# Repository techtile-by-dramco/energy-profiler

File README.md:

# 🔍 Energy Profiler 🔍

This repository contains 
- the **hardware** files (including the controller board)
- the **firmware** running on the controller board
- the **publisher script** (which receives information from the controller board over a USB connection)
- an example **subscriber script**

### Updates ToDo 📝
- ???

### Test Energy Profiler script
1. Test `/publisher-script/main_last.py`
2. Run services
	1. Copy service files to systemd:
	```
	sudo cp ~/energy-profiler/ep.service /lib/systemd/system/
 	```
 	2. Enable and start services
  	```
   	sudo systemctl enable ep.service
   	sudo systemctl start ep.service
  	```   
### Update energy profiler service
	
```
sudo cp ~/energy-profiler/ep.service /etc/systemd/system/
sudo systemctl daemon-reload
sudo systemctl restart ep.service
```

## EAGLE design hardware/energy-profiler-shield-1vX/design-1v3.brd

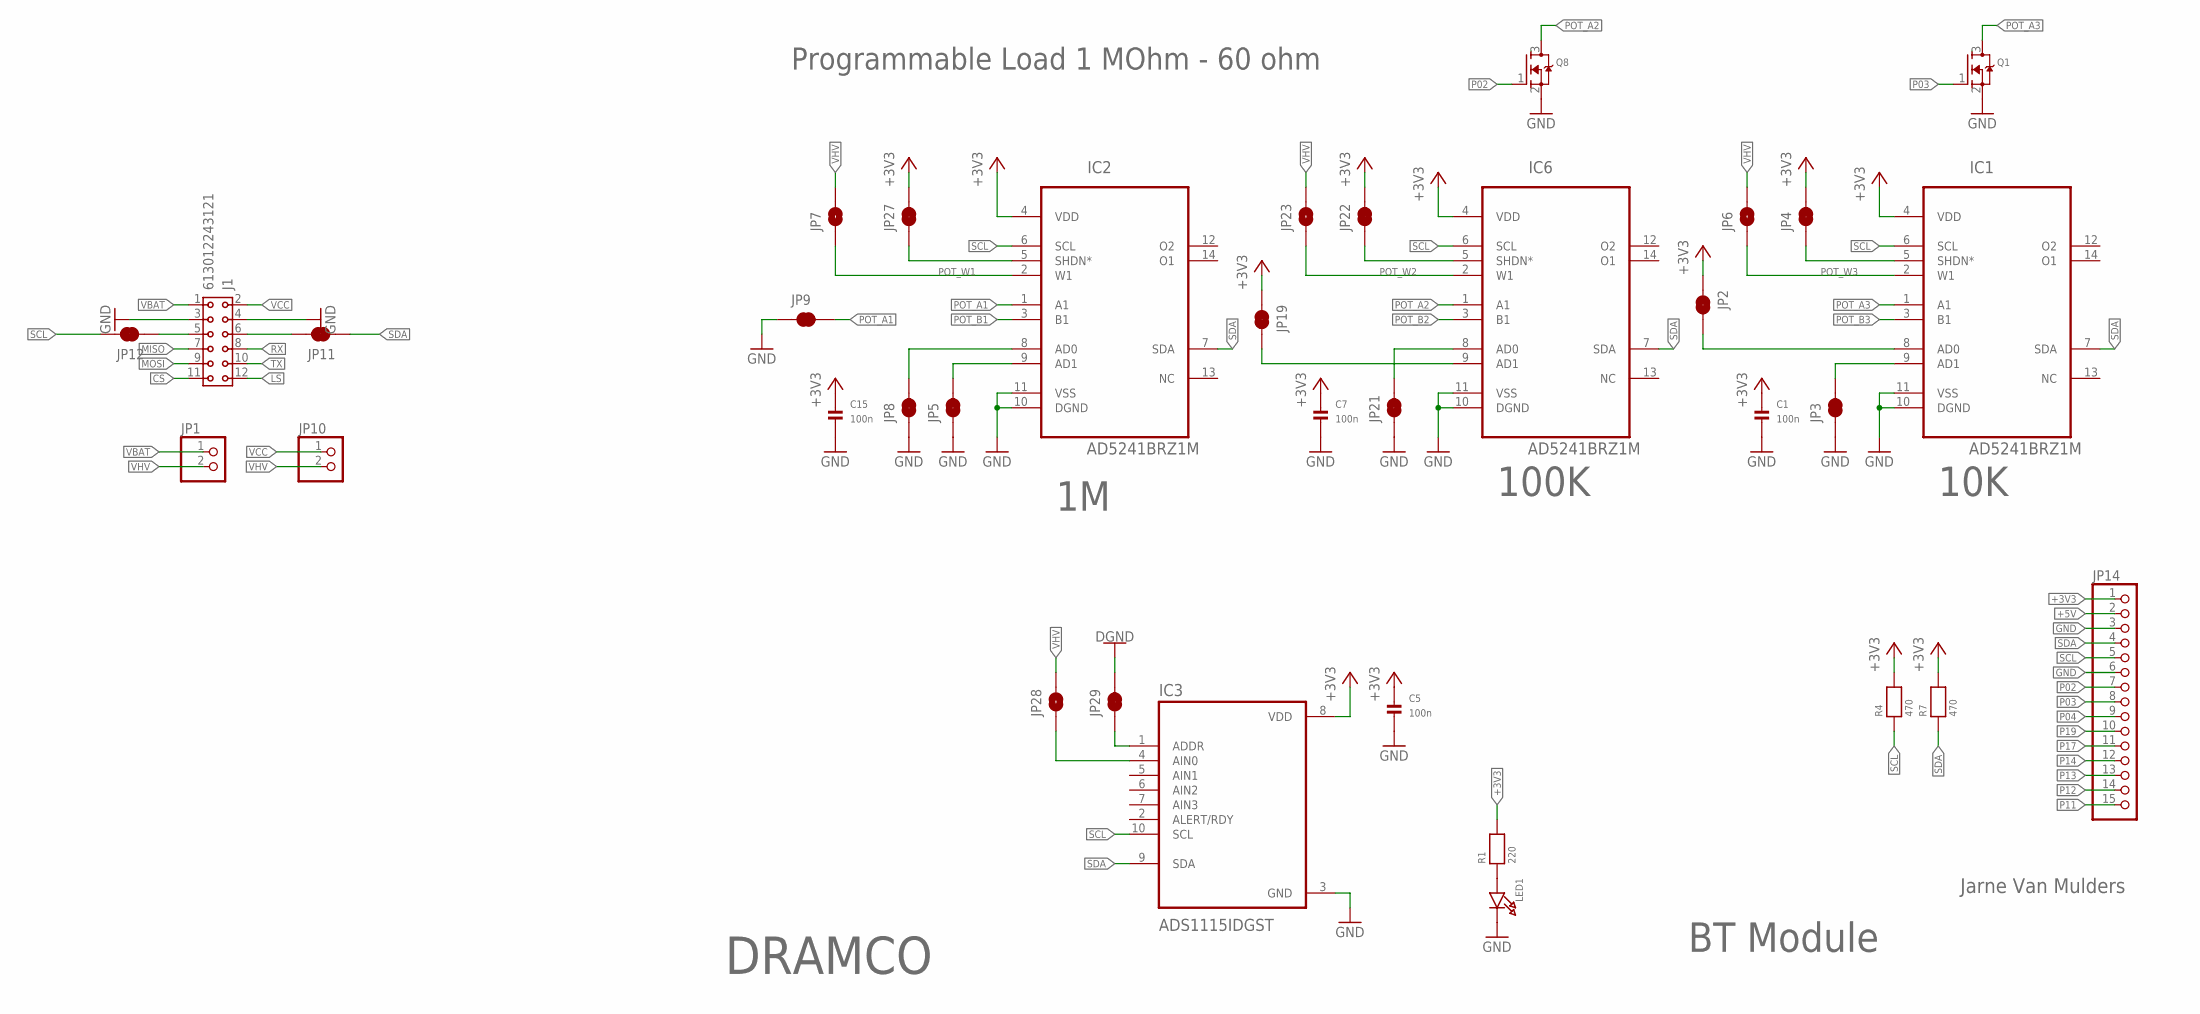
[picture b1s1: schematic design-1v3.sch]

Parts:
C1, C5, C7, C15: 100n; 0603
IC1, IC2, IC6: AD5241BRZ1M; SOIC127P600X175-14N
IC3: ADS1115IDGST; SOP50P490X110-10N
J1: 613012243121
JP1, JP10: HEADER-1X2ROUND; 1X02_ROUND
JP2, JP3, JP4, JP5, JP8, JP9, JP11, JP12, JP19, JP21, JP22, JP27, JP29: JUMPER-SMT_2_NC_TRACE_NO-SILK; SMT-JUMPER_2_NC_TRACE_NO-SILK
JP6, JP7, JP23, JP28: JUMPER-SMT_2_NO_NO-SILK; SMT-JUMPER_2_NO_NO-SILK
JP14: HEADER-1X15; 1X15_ROUND_70
LED1: LED0805; CHIPLED_0805
Q1, Q8: MOSFET-NREFLOW; SOT23-R
R1: 220; 0603
R4, R7: 470; 0603

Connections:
+3V3: C1.1, C5.1, C7.1, C15.1, IC1.4 (VDD), IC2.4 (VDD), IC3.8 (VDD), IC6.4 (VDD), JP2.1, JP4.2, JP14.1, JP19.1, JP22.2, JP27.2, R1.2, R4.2, R7.2
+5V: JP14.2
CS: J1.11
GND: C1.2, C5.2, C7.2, C15.2, IC1.10 (DGND), IC1.11 (VSS), IC2.10 (DGND), IC2.11 (VSS), IC3.3 (GND), IC6.10 (DGND), IC6.11 (VSS), J1.3, J1.4, JP3.1, JP5.1, JP8.1, JP9.1, JP14.3, JP14.6, JP21.1, JP29.2, LED1.C, Q1.2 (S), Q8.2 (S)
LS: J1.12
MISO: J1.7
MOSI: J1.9
unnamed: IC1.8 (AD0), JP2.2
unnamed: IC1.9 (AD1), JP3.2
unnamed: IC1.5 (SHDN*), JP4.1
unnamed: J1.5, JP12.1
unnamed: J1.6, JP11.2
unnamed: IC6.9 (AD1), JP19.2
unnamed: IC6.8 (AD0), JP21.2
unnamed: IC2.5 (SHDN*), JP27.1
unnamed: IC2.8 (AD0), JP8.2
unnamed: IC2.9 (AD1), JP5.2
unnamed: LED1.A, R1.1
unnamed: IC3.4 (AIN0), JP28.1
unnamed: IC3.1 (ADDR), JP29.1
unnamed: IC6.5 (SHDN*), JP22.1
P02: JP14.7, Q8.1 (G)
P03: JP14.8, Q1.1 (G)
P04: JP14.9
P11: JP14.15
P12: JP14.14
P13: JP14.13
P14: JP14.12
P17: JP14.11
P19: JP14.10
POT_A1: IC2.1 (A1), JP9.2
POT_A2: IC6.1 (A1), Q8.3 (D)
POT_A3: IC1.1 (A1), Q1.3 (D)
POT_B1: IC2.3 (B1)
POT_B2: IC6.3 (B1)
POT_B3: IC1.3 (B1)
POT_W1: IC2.2 (W1), JP7.1
POT_W2: IC6.2 (W1), JP23.1
POT_W3: IC1.2 (W1), JP6.1
RX: J1.8
SCL: IC1.6 (SCL), IC2.6 (SCL), IC3.10 (SCL), IC6.6 (SCL), JP12.2, JP14.5, R4.1
SDA: IC1.7 (SDA), IC2.7 (SDA), IC3.9 (SDA), IC6.7 (SDA), JP11.1, JP14.4, R7.1
TX: J1.10
VBAT: J1.1, JP1.1
VCC: J1.2, JP10.1
VHV: JP1.2, JP6.2, JP7.2, JP10.2, JP23.2, JP28.2

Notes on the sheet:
BT Module
Jarne Van Mulders
DRAMCO
100K
10K
Programmable Load 1 MOhm - 60 ohm

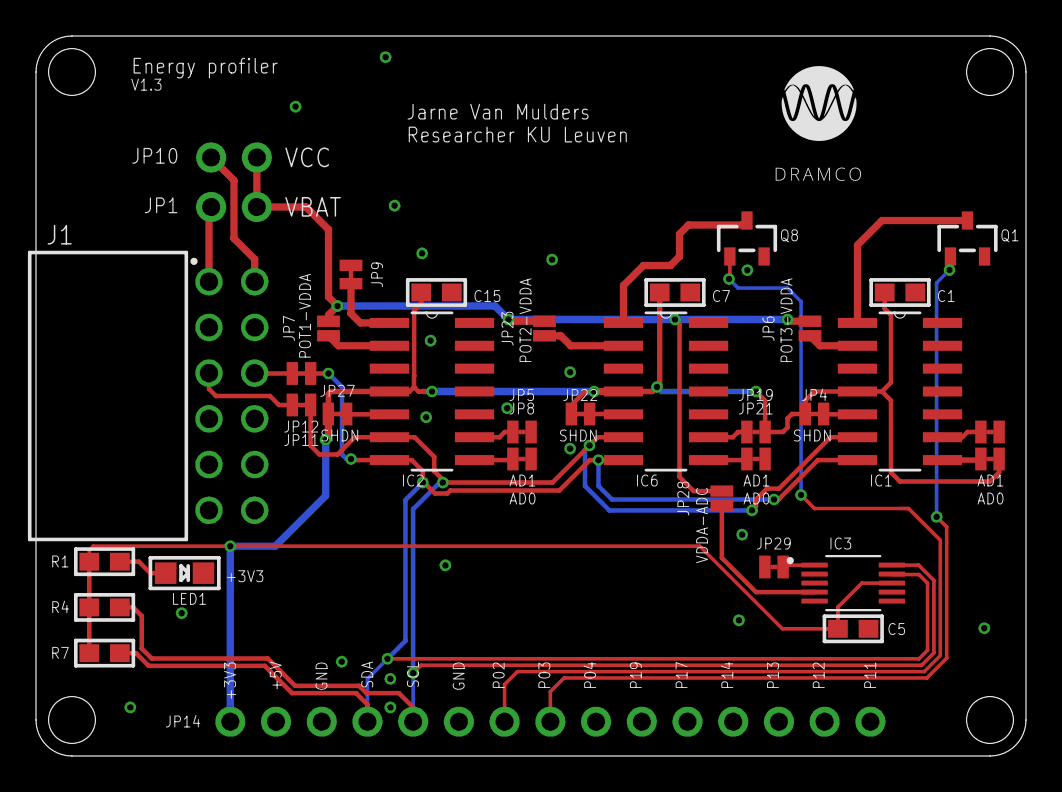
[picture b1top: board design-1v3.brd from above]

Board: 2 copper layers, 55.0 x 40.0 mm, 35 parts (0 on the bottom side), 29 nets.

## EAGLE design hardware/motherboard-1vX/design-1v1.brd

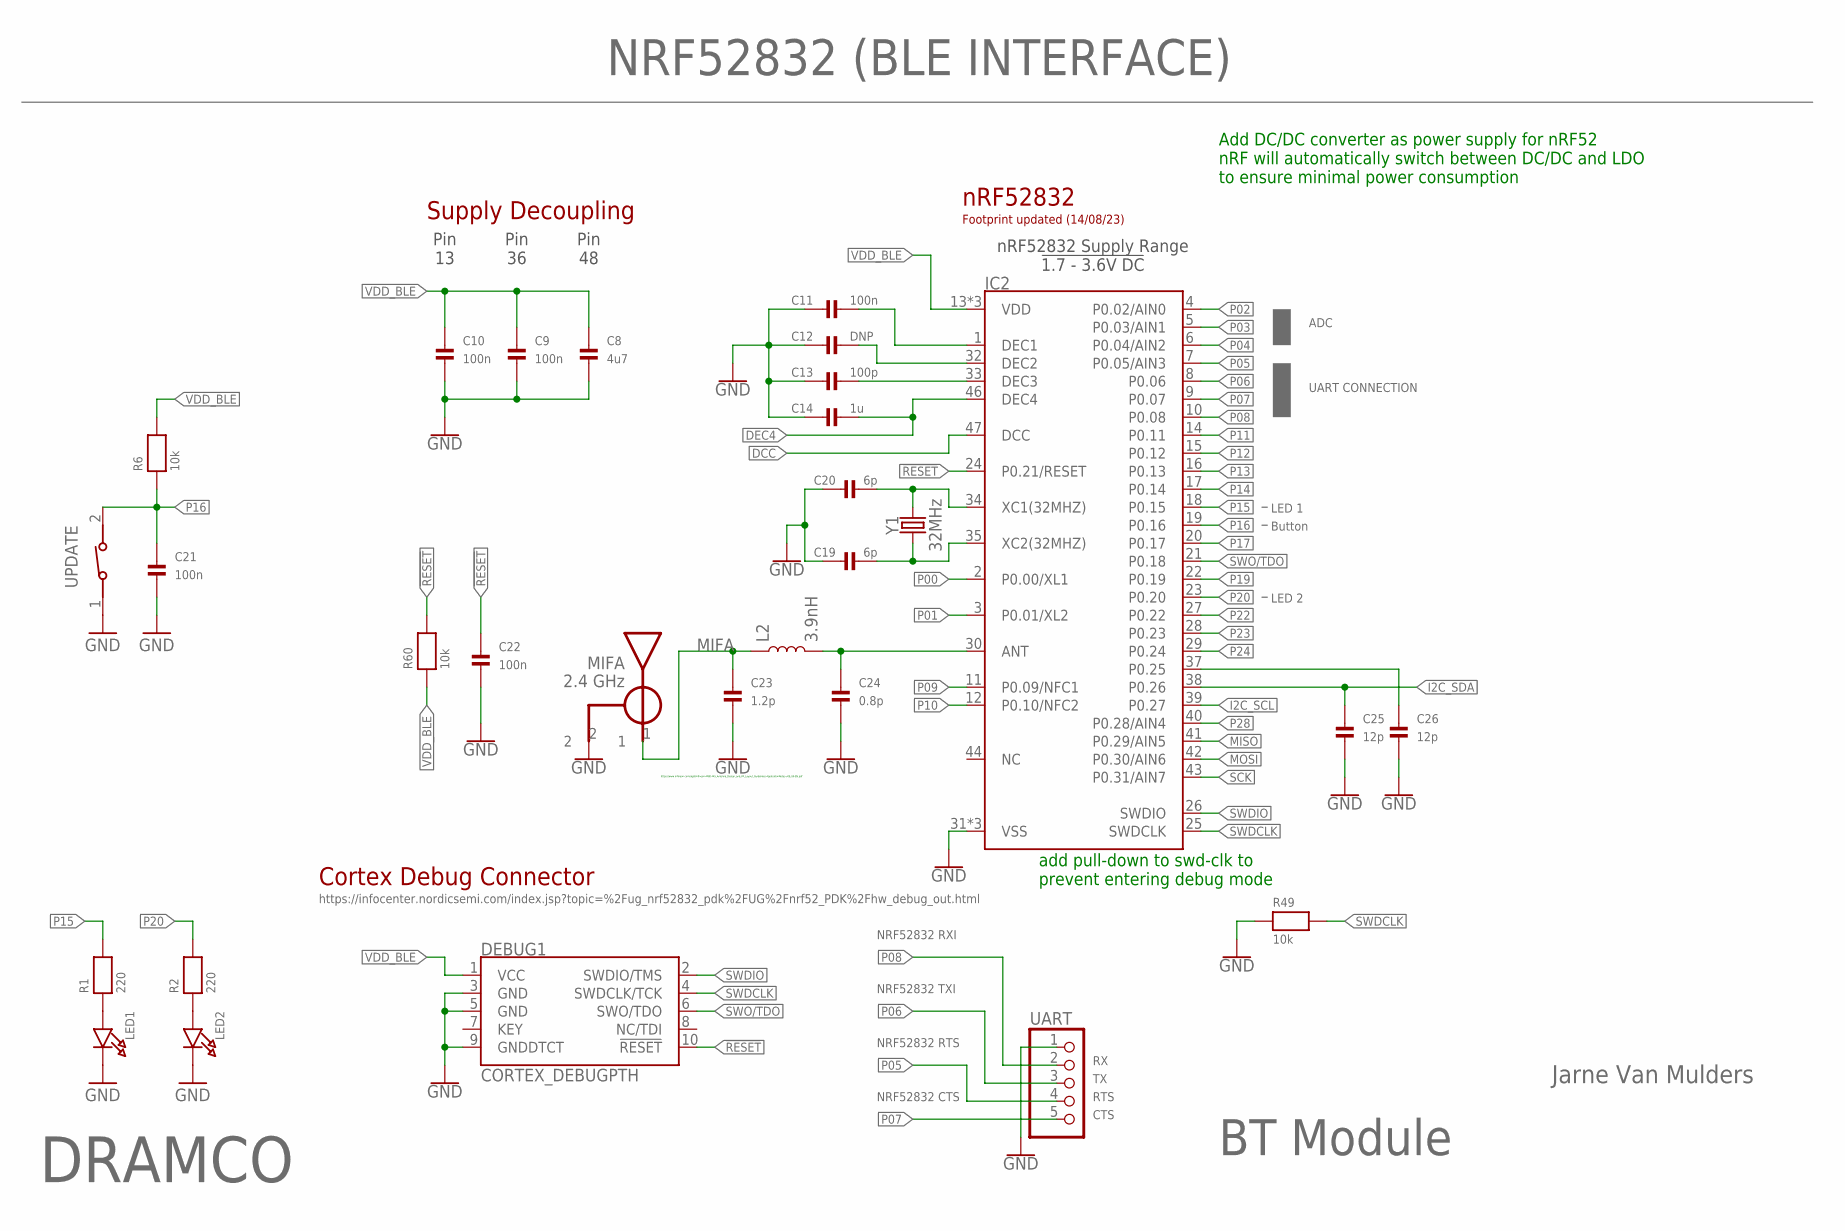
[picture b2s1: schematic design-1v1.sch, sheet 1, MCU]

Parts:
C8: 4u7; 0603
C9, C10, C11, C21, C22: 100n; 0402
C12: DNP; 0402
C13: 100p; 0402
C14: 1u; 0402
C19, C20: 6p; 0402
C23: 1.2p; 0402
C24: 0.8p; 0402
C25, C26: 12p; 0402
DEBUG1: CORTEX_DEBUGPTH; 2X5-PTH-1.27MM
IC2: NRF52832-EXTENDED; QFN48-6X6MM-EXTENDED
L2: 3.9nH; 0402
LED1, LED2: LED0805; CHIPLED_0805
R1, R2: 220; 0603
R6, R49, R60: 10k; 0402
U$18: BLE-ANT; ANT-2G4
UART: HEADER-1X5ROUND; 1X05_ROUND
UPDATE: 434111043826
Y1: 32MHz; CRYSTAL-SMD-2.0X1.6MM

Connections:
!RESET!: C22.1, DEBUG1.10 (!RESET), IC2.24 (P0.21/RESET), R60.2
ANT: C24.1, IC2.30 (ANT), L2.2
DCC: IC2.47 (DCC)
DEC4: C14.2, IC2.46 (DEC4)
DEC5: C11.2, IC2.1 (DEC1)
DEC6: C12.2, IC2.32 (DEC2)
DEC8: C13.2, IC2.33 (DEC3)
GND: C8.2, C9.2, C10.2, C11.1, C12.1, C13.1, C14.1, C19.1, C20.1, C21.2, C22.2, C23.2, C24.2, C25.2, C26.2, DEBUG1.3 (GND), DEBUG1.5 (GND), DEBUG1.9 (GNDDTCT), IC2.31 (VSS), IC2.45 (VSS), IC2.EP (VSS), LED1.C, LED2.C, R49.1, U$18.2, UART.1, UPDATE.1; also elsewhere on the board
I2C_SCL: IC2.39 (P0.27); also elsewhere on the board
I2C_SDA: C25.1, IC2.38 (P0.26); also elsewhere on the board
MIFA: C23.1, L2.1, U$18.1
MISO: IC2.41 (P0.29/AIN5)
MOSI: IC2.42 (P0.30/AIN6)
unnamed: LED2.A, R2.1
unnamed: LED1.A, R1.1
unnamed: C26.1, IC2.37 (P0.25)
P00: IC2.2 (P0.00/XL1)
P01: IC2.3 (P0.01/XL2)
P02: IC2.4 (P0.02/AIN0); also elsewhere on the board
P03: IC2.5 (P0.03/AIN1); also elsewhere on the board
P04: IC2.6 (P0.04/AIN2); also elsewhere on the board
P05: IC2.7 (P0.05/AIN3), UART.4
P06: IC2.8 (P0.06), UART.3; also elsewhere on the board
P07: IC2.9 (P0.07), UART.5
P08: IC2.10 (P0.08), UART.2; also elsewhere on the board
P09: IC2.11 (P0.09/NFC1)
P10: IC2.12 (P0.10/NFC2)
P11: IC2.14 (P0.11); also elsewhere on the board
P12: IC2.15 (P0.12); also elsewhere on the board
P13: IC2.16 (P0.13); also elsewhere on the board
P14: IC2.17 (P0.14); also elsewhere on the board
P15: IC2.18 (P0.15), R1.2
P16: C21.1, IC2.19 (P0.16), R6.1, UPDATE.2
P17: IC2.20 (P0.17); also elsewhere on the board
P19: IC2.22 (P0.19); also elsewhere on the board
P20: IC2.23 (P0.20), R2.2
P22: IC2.27 (P0.22)
P23: IC2.28 (P0.23)
P24: IC2.29 (P0.24)
P28: IC2.40 (P0.28/AIN4)
SCK: IC2.43 (P0.31/AIN7)
SWDCLK: DEBUG1.4 (SWDCLK/TCK), IC2.25 (SWDCLK), R49.2
SWDIO: DEBUG1.2 (SWDIO/TMS), IC2.26 (SWDIO)
SWO/TDO: DEBUG1.6 (SWO/TDO), IC2.21 (P0.18)
VDD_BLE: C8.1, C9.1, C10.1, DEBUG1.1 (VCC), IC2.13 (VDD), IC2.36 (VDD), IC2.48 (VDD), R6.2, R60.1; also elsewhere on the board
XC1: C20.2, IC2.34 (XC1(32MHZ)), Y1.3 (2)
XC2: C19.2, IC2.35 (XC2(32MHZ)), Y1.1

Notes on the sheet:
BT Module
Jarne Van Mulders
DRAMCO
NRF52832 (BLE INTERFACE)
Pin 13
Pin 36
Pin 48
nRF52832
Supply Decoupling
Cortex Debug Connector
nRF52832 Supply Range !1.7 - 3.6V DC!
Add DC/DC converter as power supply for nRF52 nRF will automatically switch between DC/DC and LDO to ensure minimal power consumption
add pull-down to swd-clk to prevent entering debug mode
NRF52832 RXI
NRF52832 TXI
NRF52832 RTS
NRF52832 CTS
RTS
CTS
UART CONNECTION
Button
ADC
https://www.infineon.com/dgdl/Infineon-AN91445_Antenna_Design_and_RF_Layout_Guidelines-ApplicationNotes-v09_00-EN.pdf
https://infocenter.nordicsemi.com/index.jsp?topic=%2Fug_nrf52832_pdk%2FUG%2Fnrf52_PDK%2Fhw_debug_out.html
Footprint updated (14/08/23)
LED 1
LED 2

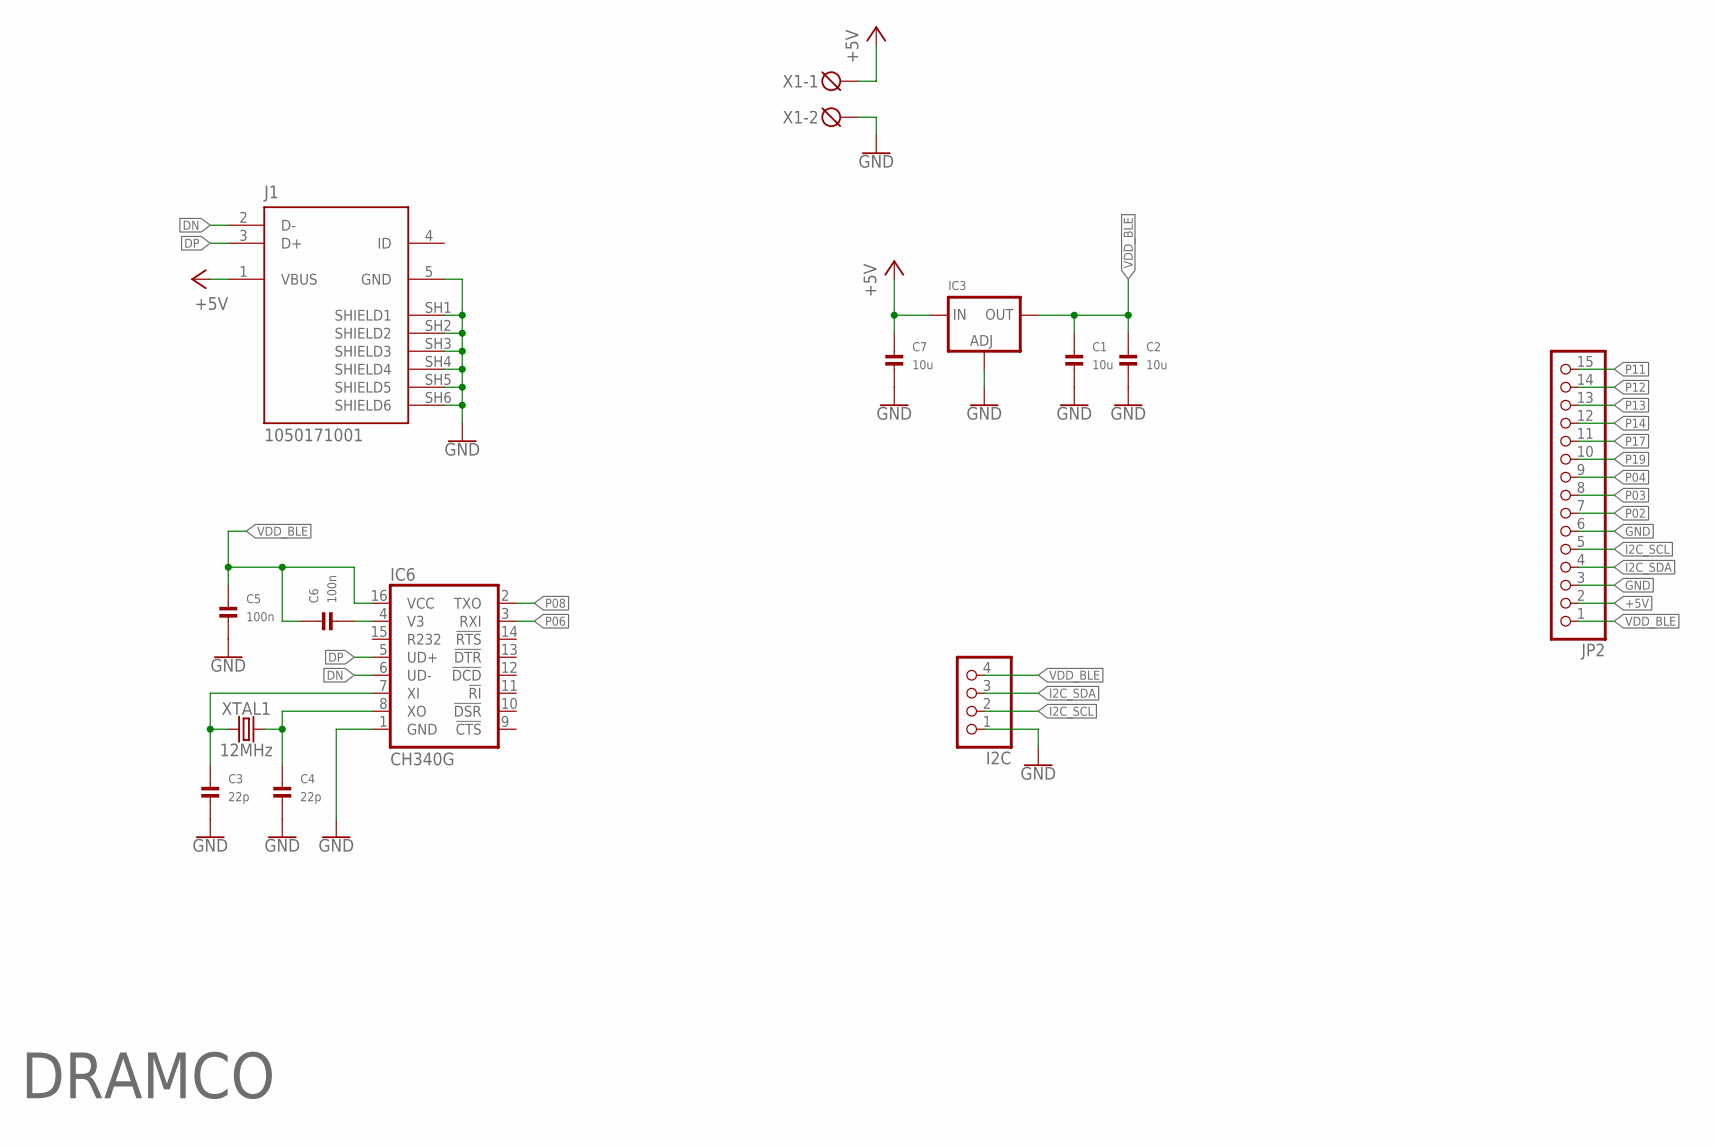
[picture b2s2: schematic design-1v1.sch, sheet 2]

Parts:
C1, C2, C7: 10u; 0805
C3, C4: 22p; 0402
C5, C6: 100n; 0402
I2C: HEADER-1X4ROUND; 1X04_ROUND
IC3: LM1117SOT223-REFLOW; SOT223-R
IC6: CH340G; SO016
J1: 1050171001; MOLEX_1050171001
JP2: HEADER-1X15; 1X15_ROUND_70
X1: DG3XX-02-3.5; DG350-3.5-02P
XTAL1: 12MHz; CRYSTAL-SMD-3.2X2.5MM

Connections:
+5V: C7.1, IC3.3 (IN), J1.1 (VBUS), JP2.2, X1.1
DN: IC6.6 (UD-), J1.2 (D-)
DP: IC6.5 (UD+), J1.3 (D+)
GND: C1.2, C2.2, C3.2, C4.2, C5.2, C7.2, I2C.1, IC3.1 (ADJ), IC6.1 (GND), J1.5 (GND), J1.SH1 (SHIELD1), J1.SH2 (SHIELD2), J1.SH3 (SHIELD3), J1.SH4 (SHIELD4), J1.SH5 (SHIELD5), J1.SH6 (SHIELD6), JP2.3, JP2.6, X1.2; also elsewhere on the board
I2C_SCL: I2C.2, JP2.5; also elsewhere on the board
I2C_SDA: I2C.3, JP2.4; also elsewhere on the board
unnamed: C3.1, IC6.7 (XI), XTAL1.1
unnamed: C4.1, IC6.8 (XO), XTAL1.3 (2)
unnamed: C6.2, IC6.4 (V3)
P02: JP2.7; also elsewhere on the board
P03: JP2.8; also elsewhere on the board
P04: JP2.9; also elsewhere on the board
P06: IC6.3 (RXI); also elsewhere on the board
P08: IC6.2 (TXO); also elsewhere on the board
P11: JP2.15; also elsewhere on the board
P12: JP2.14; also elsewhere on the board
P13: JP2.13; also elsewhere on the board
P14: JP2.12; also elsewhere on the board
P17: JP2.11; also elsewhere on the board
P19: JP2.10; also elsewhere on the board
VDD_BLE: C1.1, C2.1, C5.1, C6.1, I2C.4, IC3.2 (OUT), IC6.16 (VCC), JP2.1; also elsewhere on the board

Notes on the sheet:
DRAMCO

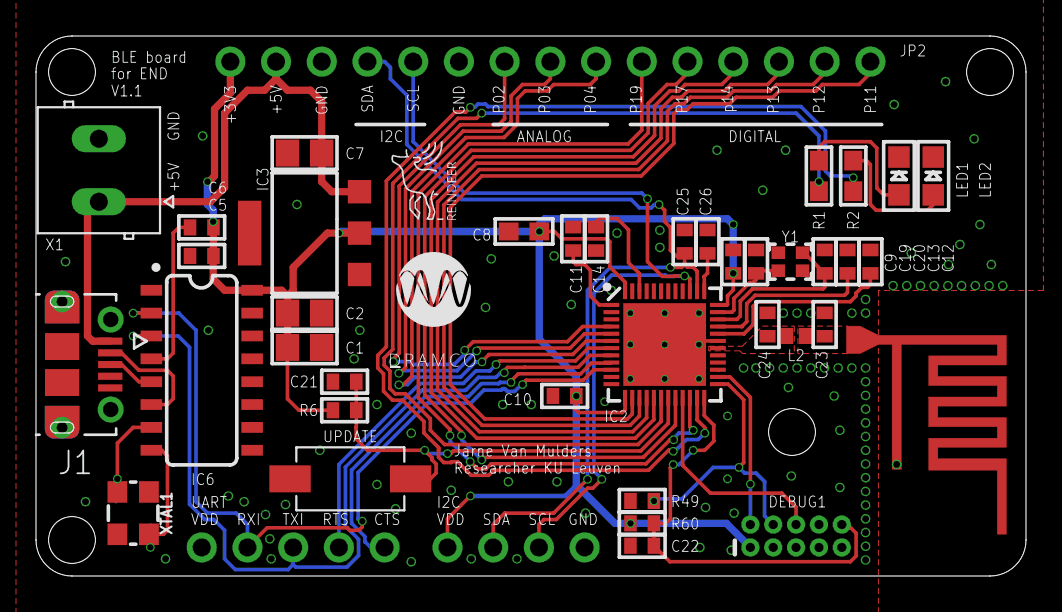
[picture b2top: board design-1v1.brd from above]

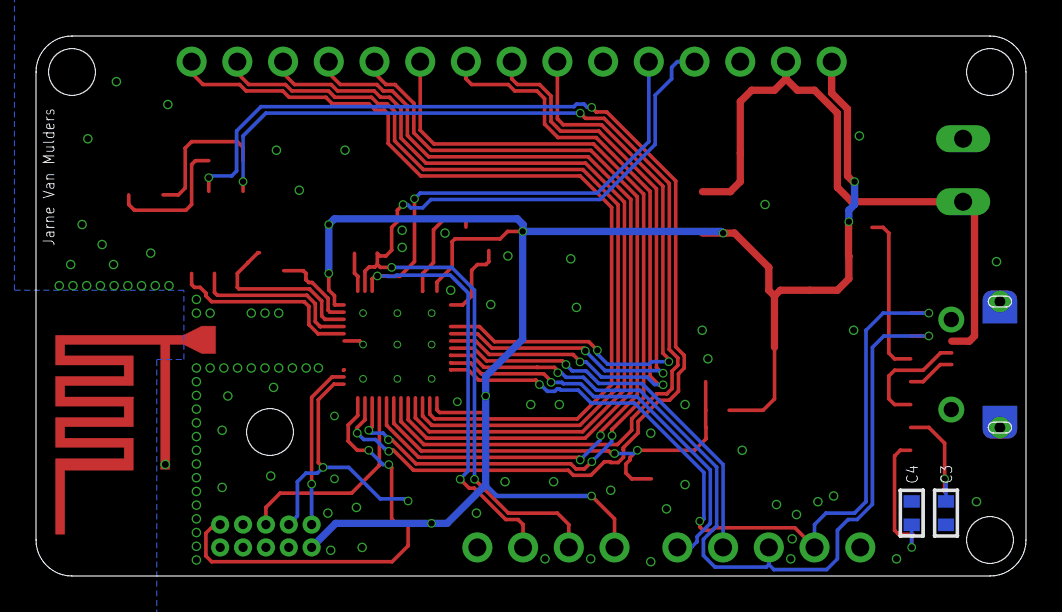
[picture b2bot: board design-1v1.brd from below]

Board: 2 copper layers, 55.0 x 30.0 mm, 43 parts (2 on the bottom side), 41 nets.

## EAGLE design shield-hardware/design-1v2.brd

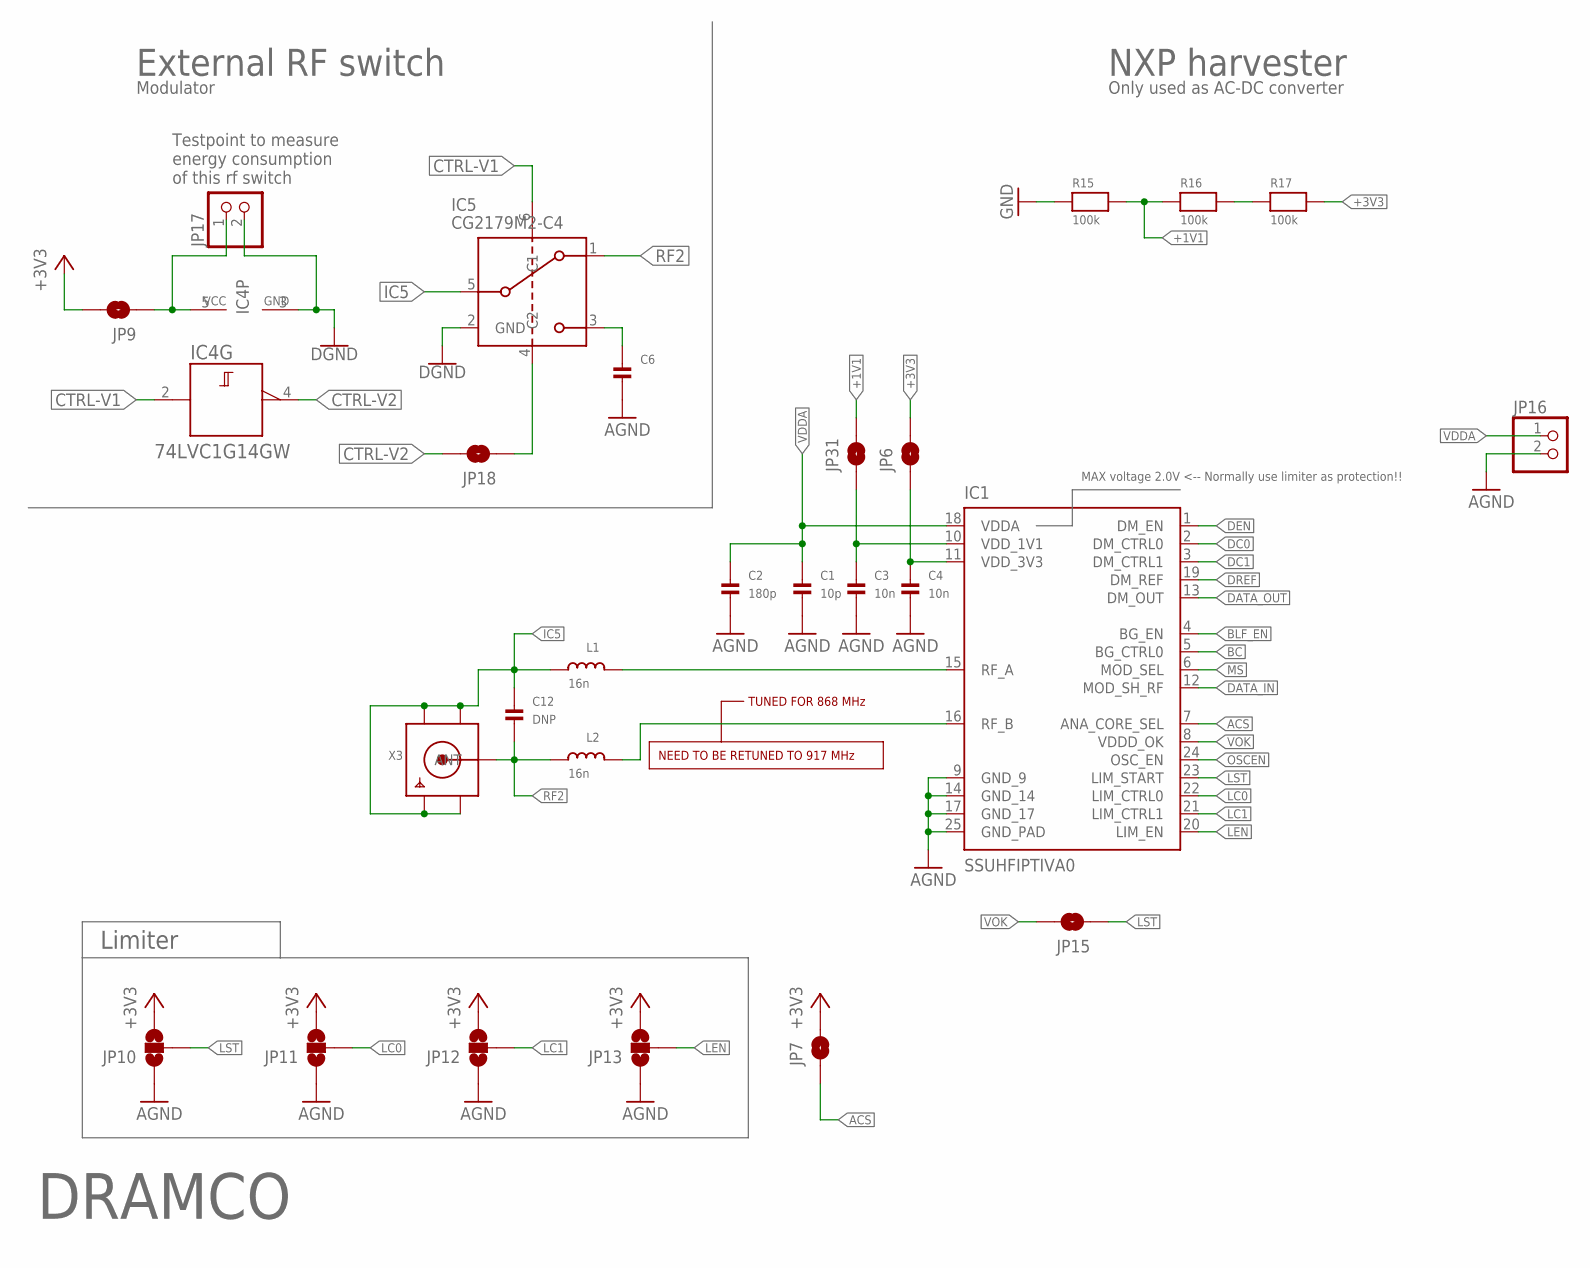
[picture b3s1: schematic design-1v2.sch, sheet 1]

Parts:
C1: 10p; 0603
C2: 180p; 0603
C3, C4: 10n; 0603
C6: CAP_CERAMIC0402; 0402
C12: DNP; 0402
IC1: SSUHFIPTIVA0; QFN50P400X400X90-25N
IC4: 74LVC1G14GW; SOT353-1
IC5: CG2179M2-C4; SC70-6-CNC04
JP6, JP7, JP9, JP15, JP18, JP31: JUMPER-SMT_2_NO_NO-SILK; SMT-JUMPER_2_NO_NO-SILK
JP10, JP11, JP12, JP13: JUMPER-SMT_3_NO_SILK; SMT-JUMPER_3_NO_SILK
JP16, JP17: HEADER-1X2ROUND; 1X02_ROUND
L1, L2: 16n; _0402
R15, R16, R17: 100k; 0603
X3: SMACONNECTOR_EDGE_UFL; SMA_EDGELAUNCH_UFL

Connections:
+1V1: JP31.2, R15.2, R16.1
+3V3: JP6.2, JP7.2, JP9.2, JP10.3, JP11.3, JP12.3, JP13.3, R17.2; also elsewhere on the board
ACS: IC1.7 (ANA_CORE_SEL), JP7.1
AGND: C1.2, C2.2, C3.2, C4.2, C6.2, IC1.9 (GND_9), IC1.14 (GND_14), IC1.17 (GND_17), IC1.25 (GND_PAD), JP10.1, JP11.1, JP12.1, JP13.1, JP16.2; also elsewhere on the board
BC: IC1.5 (BG_CTRL0)
BLF_EN: IC1.4 (BG_EN)
CTRL-V1: IC4.2 (A), IC5.6 (C1); also elsewhere on the board
CTRL-V2: IC4.4 (Y), JP18.2
DATA_IN: IC1.12 (MOD_SH_RF)
DATA_OUT: IC1.13 (DM_OUT)
DC0: IC1.2 (DM_CTRL0)
DC1: IC1.3 (DM_CTRL1)
DEN: IC1.1 (DM_EN)
DREF: IC1.19 (DM_REF)
GND: IC4.3 (GND), IC5.2 (GND), JP17.2, R15.1; also elsewhere on the board
IC5: C12.1, IC5.5 (PC), L1.1, X3.GND@1 (GND1), X3.GND@2 (GND2), X3.GND@3 (GND3), X3.GND@4 (GND4)
LC0: IC1.22 (LIM_CTRL0), JP11.2
LC1: IC1.21 (LIM_CTRL1), JP12.2
LEN: IC1.20 (LIM_EN), JP13.2
LST: IC1.23 (LIM_START), JP10.2, JP15.1
MS: IC1.6 (MOD_SEL)
unnamed: C4.1, IC1.11 (VDD_3V3), JP6.1
unnamed: C3.1, IC1.10 (VDD_1V1), JP31.1
unnamed: IC1.15 (RF_A), L1.2
unnamed: IC1.16 (RF_B), L2.2
unnamed: IC5.4 (C2), JP18.1
unnamed: C6.1, IC5.3 (P2)
unnamed: IC4.5 (VCC), JP9.1, JP17.1
unnamed: R16.2, R17.1
OSCEN: IC1.24 (OSC_EN)
RF2: C12.2, IC5.1, L2.1, X3.P (ANT)
VDDA: C1.1, C2.1, IC1.18 (VDDA), JP16.1; also elsewhere on the board
VOK: IC1.8 (VDDD_OK), JP15.2

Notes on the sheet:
Limiter
MAX voltage 2.0V <-- Normally use limiter as protection!!
TUNED FOR 868 MHz
NEED TO BE RETUNED TO 917 MHz
NXP harvester
Only used as AC-DC converter
DRAMCO
External RF switch
Modulator
Testpoint to measure energy consumption of this rf switch

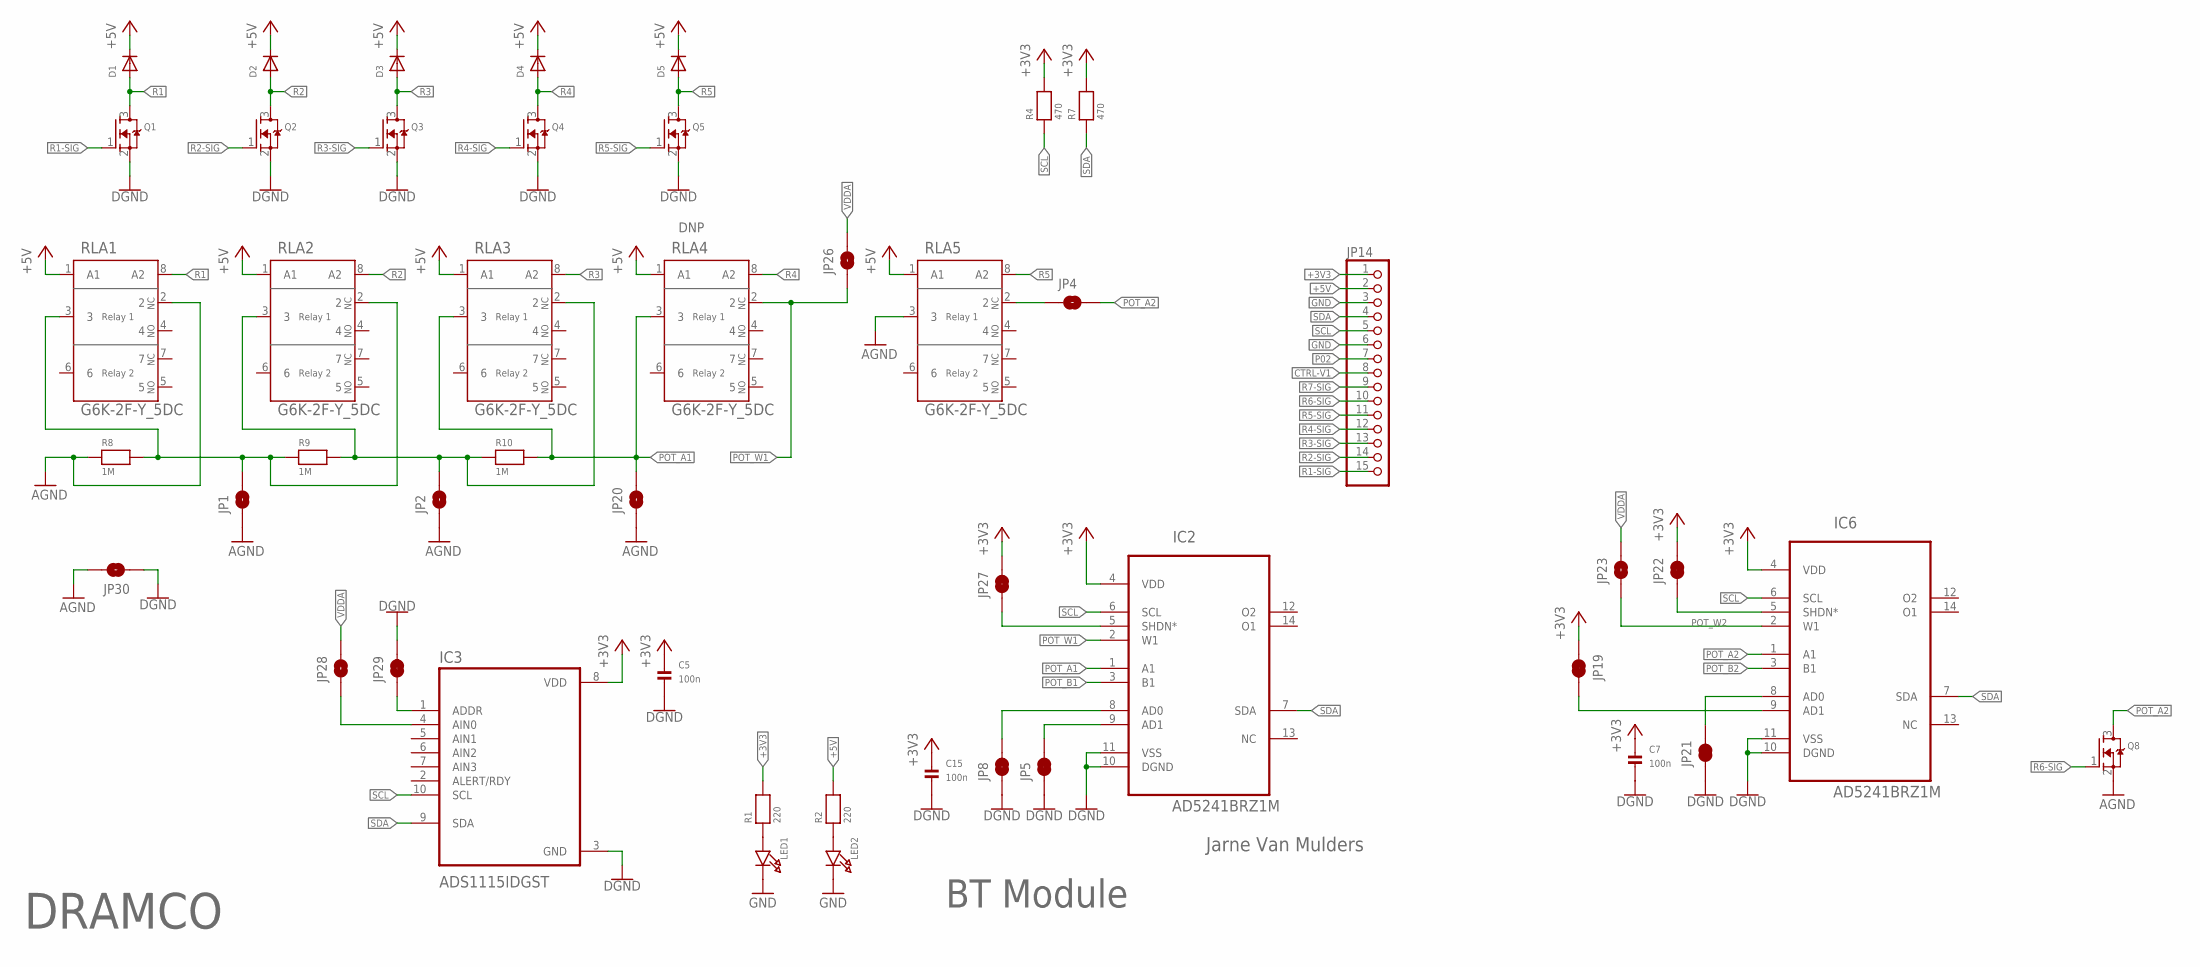
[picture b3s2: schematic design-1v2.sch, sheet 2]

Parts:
C5, C7, C15: 100n; 0603
D1, D2, D3, D4, D5: DIODESOD-123; SOD-123
IC2, IC6: AD5241BRZ1M; SOIC127P600X175-14N
IC3: ADS1115IDGST; SOP50P490X110-10N
JP1, JP2, JP4, JP20, JP23, JP26, JP28, JP30: JUMPER-SMT_2_NO_NO-SILK; SMT-JUMPER_2_NO_NO-SILK
JP5, JP8, JP19, JP21, JP22, JP27, JP29: JUMPER-SMT_2_NC_TRACE_NO-SILK; SMT-JUMPER_2_NC_TRACE_NO-SILK
JP14: HEADER-1X15; 1X15_ROUND_70
LED1, LED2: LED0805; CHIPLED_0805
Q1, Q2, Q3, Q4, Q5, Q8: MOSFET-NREFLOW; SOT23-R
R1, R2: 220; 0603
R4, R7: 470; 0603
R8, R9, R10: 1M; 0805
RLA1, RLA2, RLA3, RLA4, RLA5: G6K-2F-Y_5DC; RELAY_G6K-2F_OMR

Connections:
+3V3: C5.1, C7.1, C15.1, IC2.4 (VDD), IC3.8 (VDD), IC6.4 (VDD), JP14.1, JP19.1, JP22.2, JP27.2, R1.2, R4.2, R7.2; also elsewhere on the board
+5V: D1.C, D2.C, D3.C, D4.C, D5.C, JP14.2, R2.2, RLA1.1 (A1), RLA2.1 (A1), RLA3.1 (A1), RLA4.1 (A1), RLA5.1 (A1)
AGND: JP1.1, JP2.1, JP20.1, JP30.2, Q8.2 (S), R8.1, RLA1.2, RLA5.3; also elsewhere on the board
CTRL-V1: JP14.8; also elsewhere on the board
GND: C5.2, C7.2, C15.2, IC2.10 (DGND), IC2.11 (VSS), IC3.3 (GND), IC6.10 (DGND), IC6.11 (VSS), JP5.1, JP8.1, JP14.3, JP14.6, JP21.1, JP29.2, JP30.1, LED1.C, LED2.C, Q1.2 (S), Q2.2 (S), Q3.2 (S), Q4.2 (S), Q5.2 (S); also elsewhere on the board
unnamed: LED2.A, R2.1
unnamed: JP2.2, R9.2, R10.1, RLA2.3, RLA3.2
unnamed: IC6.9 (AD1), JP19.2
unnamed: JP1.2, R8.2, R9.1, RLA1.3, RLA2.2
unnamed: IC6.8 (AD0), JP21.2
unnamed: JP4.1, RLA5.2
unnamed: IC2.5 (SHDN*), JP27.1
unnamed: IC2.8 (AD0), JP8.2
unnamed: IC2.9 (AD1), JP5.2
unnamed: LED1.A, R1.1
unnamed: IC3.4 (AIN0), JP28.1
unnamed: IC3.1 (ADDR), JP29.1
unnamed: IC6.5 (SHDN*), JP22.1
P02: JP14.7
POT_A1: IC2.1 (A1), JP20.2, R10.2, RLA3.3, RLA4.3
POT_A2: IC6.1 (A1), JP4.2, Q8.3 (D)
POT_B1: IC2.3 (B1)
POT_B2: IC6.3 (B1)
POT_W1: IC2.2 (W1), JP26.1, RLA4.2
POT_W2: IC6.2 (W1), JP23.1
R1: D1.A, Q1.3 (D), RLA1.8 (A2)
R1-SIG: JP14.15, Q1.1 (G)
R2: D2.A, Q2.3 (D), RLA2.8 (A2)
R2-SIG: JP14.14, Q2.1 (G)
R3: D3.A, Q3.3 (D), RLA3.8 (A2)
R3-SIG: JP14.13, Q3.1 (G)
R4: D4.A, Q4.3 (D), RLA4.8 (A2)
R4-SIG: JP14.12, Q4.1 (G)
R5: D5.A, Q5.3 (D), RLA5.8 (A2)
R5-SIG: JP14.11, Q5.1 (G)
R6-SIG: JP14.10, Q8.1 (G)
R7-SIG: JP14.9
SCL: IC2.6 (SCL), IC3.10 (SCL), IC6.6 (SCL), JP14.5, R4.1
SDA: IC2.7 (SDA), IC3.9 (SDA), IC6.7 (SDA), JP14.4, R7.1
VDDA: JP23.2, JP26.2, JP28.2; also elsewhere on the board

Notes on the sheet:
BT Module
Jarne Van Mulders
DRAMCO
DNP

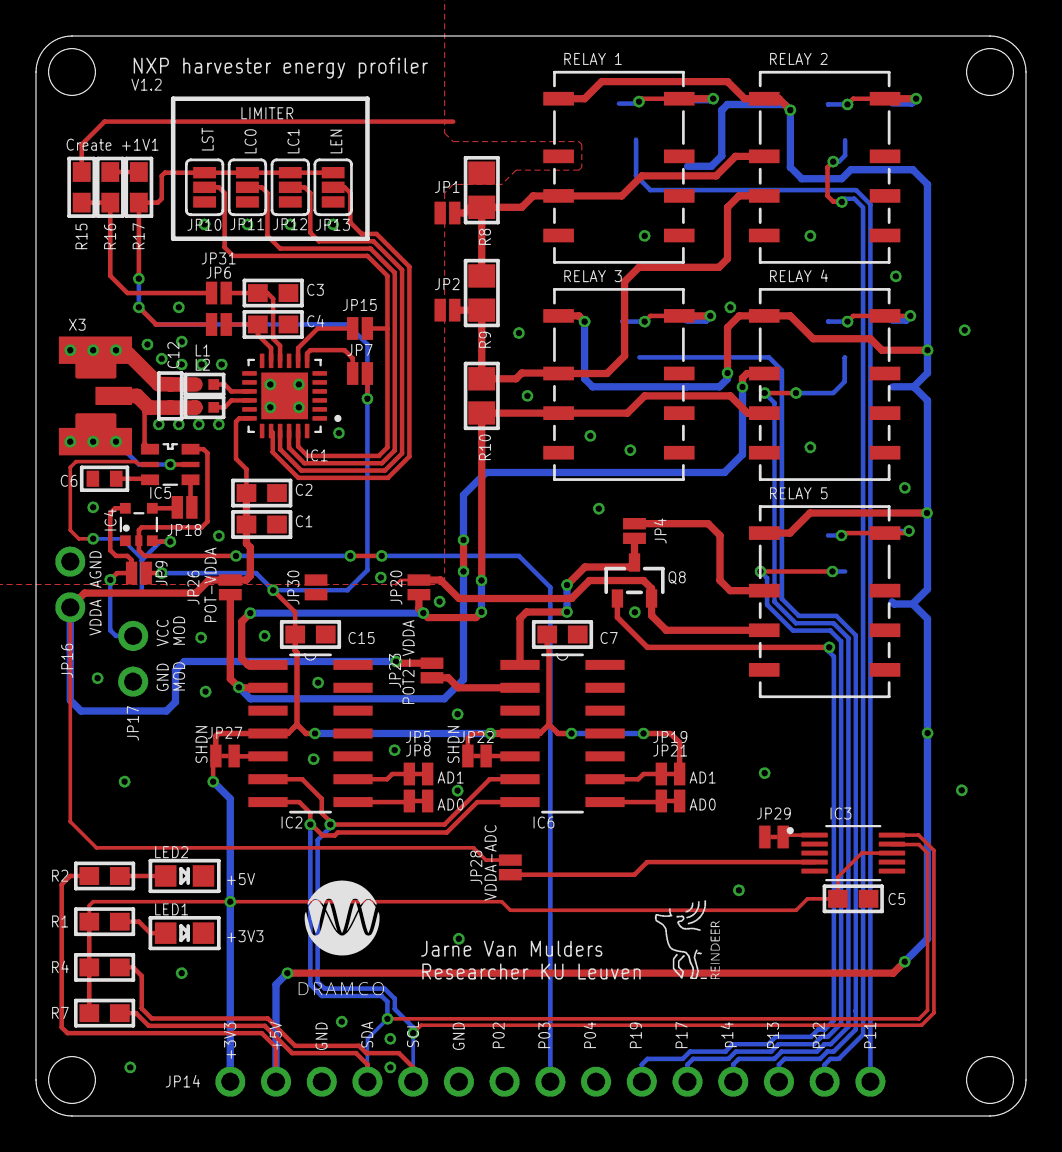
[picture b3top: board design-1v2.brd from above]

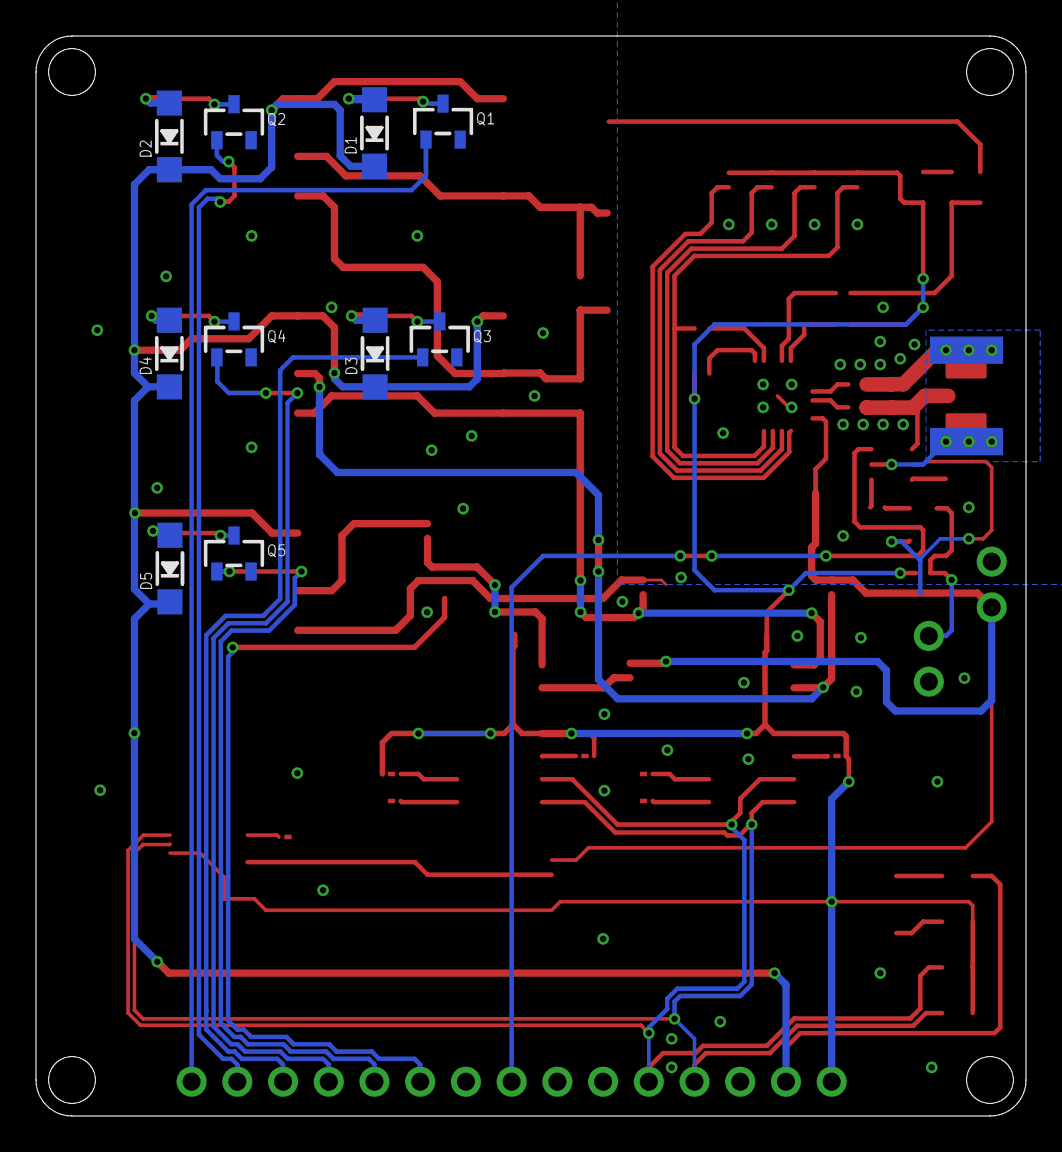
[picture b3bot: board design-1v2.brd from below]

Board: 2 copper layers, 55.0 x 60.0 mm, 74 parts (10 on the bottom side), 54 nets.

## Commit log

2025-11-27 Change serial port from ttyUSB0 to ttyUSB1
2025-11-27 Update serial port from COM4 to /dev/ttyUSB1
2025-11-27 Refactor data reading and transmission logic
    Refactor main loop and data reading process for clarity.
2025-11-27 Update read_data function for length and checksum
    Refactor read_data function to include length byte and checksum validation.
2025-11-27 Remove length print statement
    Removed debug print statement for length.
2025-11-27 Fix struct unpack format from 'LLL' to 'lll'
2025-12-11 Update README for Energy Profiler section
2025-12-11 Fix formatting in README for energy profiler service
2025-12-12 Update firmware
2025-12-12 Fix print statement to show power consumption
2026-01-19 Update README ToDo section and clarify tasks
    Remove outdated ToDo items and add a placeholder for new tasks.
2026-01-19 Update hardware folder
2026-01-19 update firmware folder
2026-03-04 Add validation results
2026-03-04 Add images and sections to README for calibration
2026-03-04 Update README with calibration details
    Added details about the HAMEG HM8112-3 connection and calibration process for the energy profiler.
2026-03-04 add 02 js measurements
2026-03-04 Add README for JouleScope Measurements
2026-03-04 Update JS measurement plots
2026-03-04 Update image link for P1 results in README
2026-03-04 Revise README for JouleScope power sweep results
    Updated section titles and added explanations for power calculations in the JouleScope measurements.
2026-03-05 Add 03
2026-03-05 Update README with JouleScope measurement images
    Added images to the README for JouleScope measurements.
2026-03-05 Update README with voltage measurement details
    Added explanation for voltage measurement with JouleScope.
2026-04-15 Add hw 1v3
2026-04-15 add validation hw 1v3

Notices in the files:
parts and their libraries:
microbuilder: This work is placed in the public domain, and may be freely used for commercial and non-commercial work with the following conditions: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
SparkFun-Jumpers: Licensing: Creative Commons ShareAlike 4.0 International - https://creativecommons.org/licenses/by-sa/4.0
